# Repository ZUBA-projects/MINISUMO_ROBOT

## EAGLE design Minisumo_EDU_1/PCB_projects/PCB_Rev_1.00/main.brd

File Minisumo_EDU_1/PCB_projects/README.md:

# MINISUMO_ROBOT_EDU1

Mainboard rev 1.10
	
```
	//in future
```

Mainboard rev 1.00

```
Bugs: 
	-bad JST balancer connector size
	-bad color sensor connector pinout
```

Eagle libraries file: https://github.com/ZUBA-projects/ZUBA_EAGLE_LBR

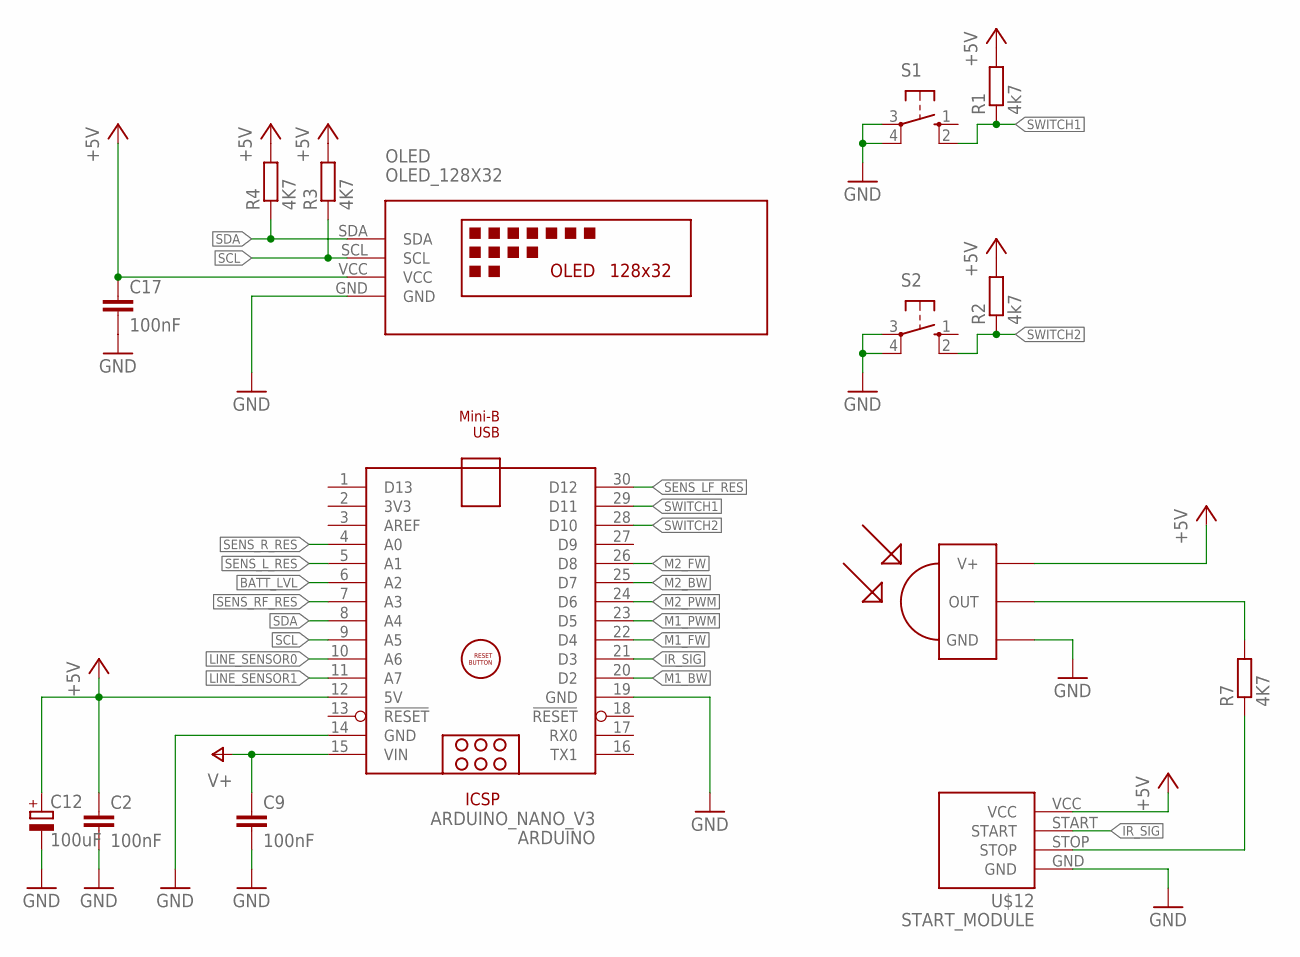
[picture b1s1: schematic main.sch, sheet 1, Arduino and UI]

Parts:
ARDUINO: ARDUINO_NANO_V3
C2, C9, C17: 100nF; C0805
C12: 100uF; E3,5-8
OLED: OLED_128X32; OLED
R1, R2: 4k7; M0805
R3, R4, R7: 4K7; M0805
S1, S2: 10-XX; B3F-10XX
U$2: TSOP4838; TSOP
U$12: START_MODULE

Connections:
+5V: ARDUINO.12 (5V), C2.1, C12.+, C17.1, OLED.VCC, R1.2, R2.2, R3.2, R4.2, U$2.VCC (V+), U$12.VCC; also elsewhere on the board
BATT_LVL: ARDUINO.6 (A2); also elsewhere on the board
GND: ARDUINO.14 (GND), ARDUINO.19 (GND), C2.2, C9.2, C12.-, C17.2, OLED.GND, S1.3, S1.4 (P1), S2.3, S2.4 (P1), U$2.GND, U$12.GND; also elsewhere on the board
IR_SIG: ARDUINO.21 (D3), U$12.START
LINE_SENSOR0: ARDUINO.10 (A6); also elsewhere on the board
LINE_SENSOR1: ARDUINO.11 (A7); also elsewhere on the board
M1_BW: ARDUINO.20 (D2); also elsewhere on the board
M1_FW: ARDUINO.22 (D4); also elsewhere on the board
M1_PWM: ARDUINO.23 (D5); also elsewhere on the board
M2_BW: ARDUINO.25 (D7); also elsewhere on the board
M2_FW: ARDUINO.26 (D8); also elsewhere on the board
M2_PWM: ARDUINO.24 (D6); also elsewhere on the board
unnamed: R7.1, U$12.STOP
unnamed: R7.2, U$2.OUT
SCL: ARDUINO.9 (A5), OLED.SCL, R3.1; also elsewhere on the board
SDA: ARDUINO.8 (A4), OLED.SDA, R4.1; also elsewhere on the board
SENS_LF_RES: ARDUINO.30 (D12); also elsewhere on the board
SENS_L_RES: ARDUINO.5 (A1); also elsewhere on the board
SENS_RF_RES: ARDUINO.7 (A3); also elsewhere on the board
SENS_R_RES: ARDUINO.4 (A0); also elsewhere on the board
SWITCH1: ARDUINO.29 (D11), R1.1, S1.2 (S1)
SWITCH2: ARDUINO.28 (D10), R2.1, S2.2 (S1)
V+: ARDUINO.15 (VIN), C9.1; also elsewhere on the board

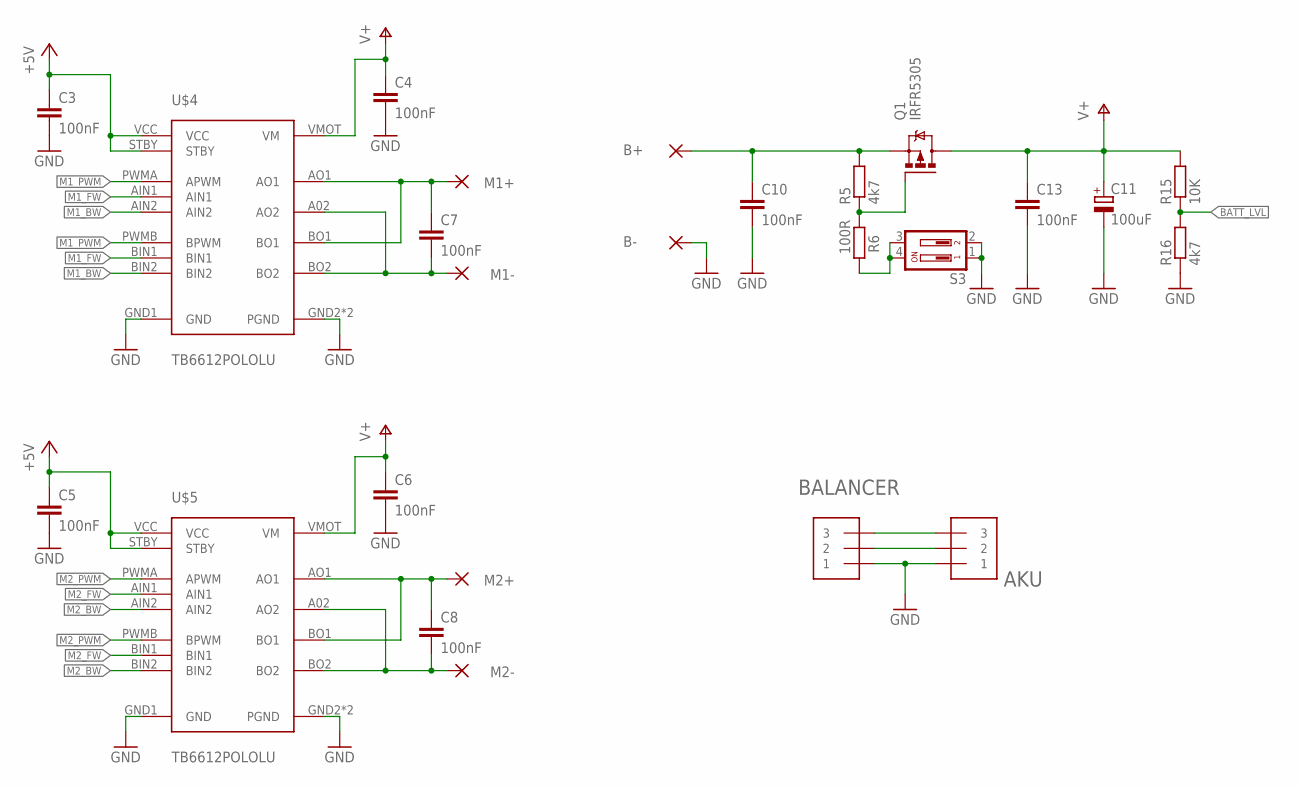
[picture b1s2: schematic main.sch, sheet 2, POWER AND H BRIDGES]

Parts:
AKU: JST_ZH_3
B+: 2,54/1,0
B-: 2,54/1,0
BALANCER: JST_ZH_3
C3, C4, C5, C6, C7, C8, C10, C13: 100nF; C0805
C11: 100uF; E3,5-8
M1+, M1-, M2+, M2-: 2,54/1,0
Q1: IRFR5305; D-PAK_TO252AA
R5, R16: 4k7; M0805
R6: 100R; M0805
R15: 10K; M0805
S3: DS02; DS-02
U$4, U$5: TB6612POLOLU; POLOLU

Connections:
+5V: C3.1, C5.1, U$4.STBY, U$4.VCC, U$5.STBY, U$5.VCC; also elsewhere on the board
BATT_LVL: R15.1, R16.2; also elsewhere on the board
GND: AKU.P$1 (1), B-.1, BALANCER.P$1 (1), C3.2, C4.2, C5.2, C6.2, C10.2, C11.-, C13.2, R16.1, S3.1, S3.2, U$4.GND1 (GND), U$4.GND2 (PGND), U$4.GND3 (PGND), U$5.GND1 (GND), U$5.GND2 (PGND), U$5.GND3 (PGND); also elsewhere on the board
M1_BW: U$4.AIN2, U$4.BIN2; also elsewhere on the board
M1_FW: U$4.AIN1, U$4.BIN1; also elsewhere on the board
M1_PWM: U$4.PWMA (APWM), U$4.PWMB (BPWM); also elsewhere on the board
M2_BW: U$5.AIN2, U$5.BIN2; also elsewhere on the board
M2_FW: U$5.AIN1, U$5.BIN1; also elsewhere on the board
M2_PWM: U$5.PWMA (APWM), U$5.PWMB (BPWM); also elsewhere on the board
unnamed: C7.1, M1+.1, U$4.AO1, U$4.BO1
unnamed: C7.2, M1-.1, U$4.A02 (AO2), U$4.BO2
unnamed: C8.1, M2+.1, U$5.AO1, U$5.BO1
unnamed: C8.2, M2-.1, U$5.A02 (AO2), U$5.BO2
unnamed: Q1.1 (G), R5.1, R6.1
unnamed: R6.2, S3.3, S3.4
unnamed: AKU.P$2 (2), BALANCER.P$2 (2)
unnamed: B+.1, C10.1, Q1.3 (S), R5.2
unnamed: AKU.P$3 (3), BALANCER.P$3 (3)
V+: C4.1, C6.1, C11.+, C13.1, Q1.4 (D), R15.2, U$4.VMOT (VM), U$5.VMOT (VM); also elsewhere on the board

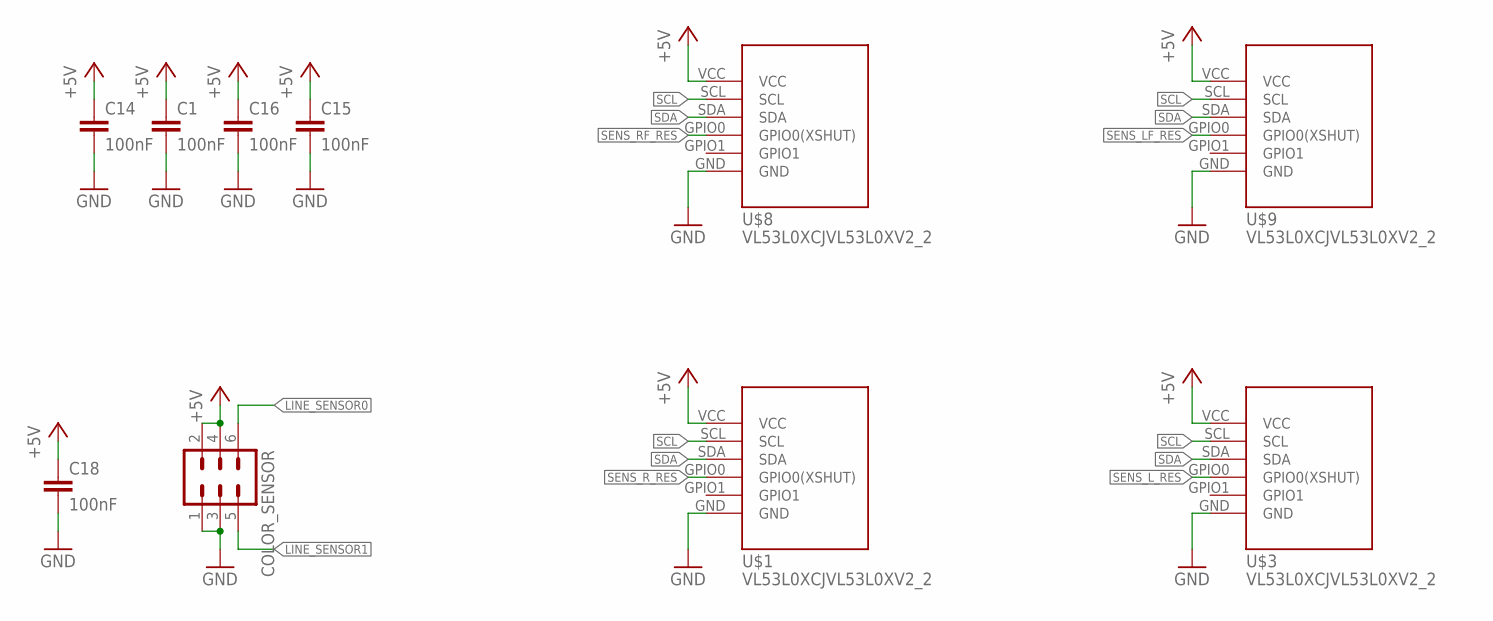
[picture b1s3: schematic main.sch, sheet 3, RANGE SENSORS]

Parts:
C1, C14, C15, C16, C18: 100nF; C0805
COLOR_SENSOR: MA03-2
U$1, U$3, U$8, U$9: VL53L0XCJVL53L0XV2_2; VL53L0X_4

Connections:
+5V: C1.1, C14.1, C15.1, C16.1, C18.1, COLOR_SENSOR.2, COLOR_SENSOR.4, U$1.VCC, U$3.VCC, U$8.VCC, U$9.VCC; also elsewhere on the board
GND: C1.2, C14.2, C15.2, C16.2, C18.2, COLOR_SENSOR.1, COLOR_SENSOR.3, U$1.GND, U$3.GND, U$8.GND, U$9.GND; also elsewhere on the board
LINE_SENSOR0: COLOR_SENSOR.6; also elsewhere on the board
LINE_SENSOR1: COLOR_SENSOR.5; also elsewhere on the board
SCL: U$1.SCL, U$3.SCL, U$8.SCL, U$9.SCL; also elsewhere on the board
SDA: U$1.SDA, U$3.SDA, U$8.SDA, U$9.SDA; also elsewhere on the board
SENS_LF_RES: U$9.GPIO0 (GPIO0(XSHUT)); also elsewhere on the board
SENS_L_RES: U$3.GPIO0 (GPIO0(XSHUT)); also elsewhere on the board
SENS_RF_RES: U$8.GPIO0 (GPIO0(XSHUT)); also elsewhere on the board
SENS_R_RES: U$1.GPIO0 (GPIO0(XSHUT)); also elsewhere on the board

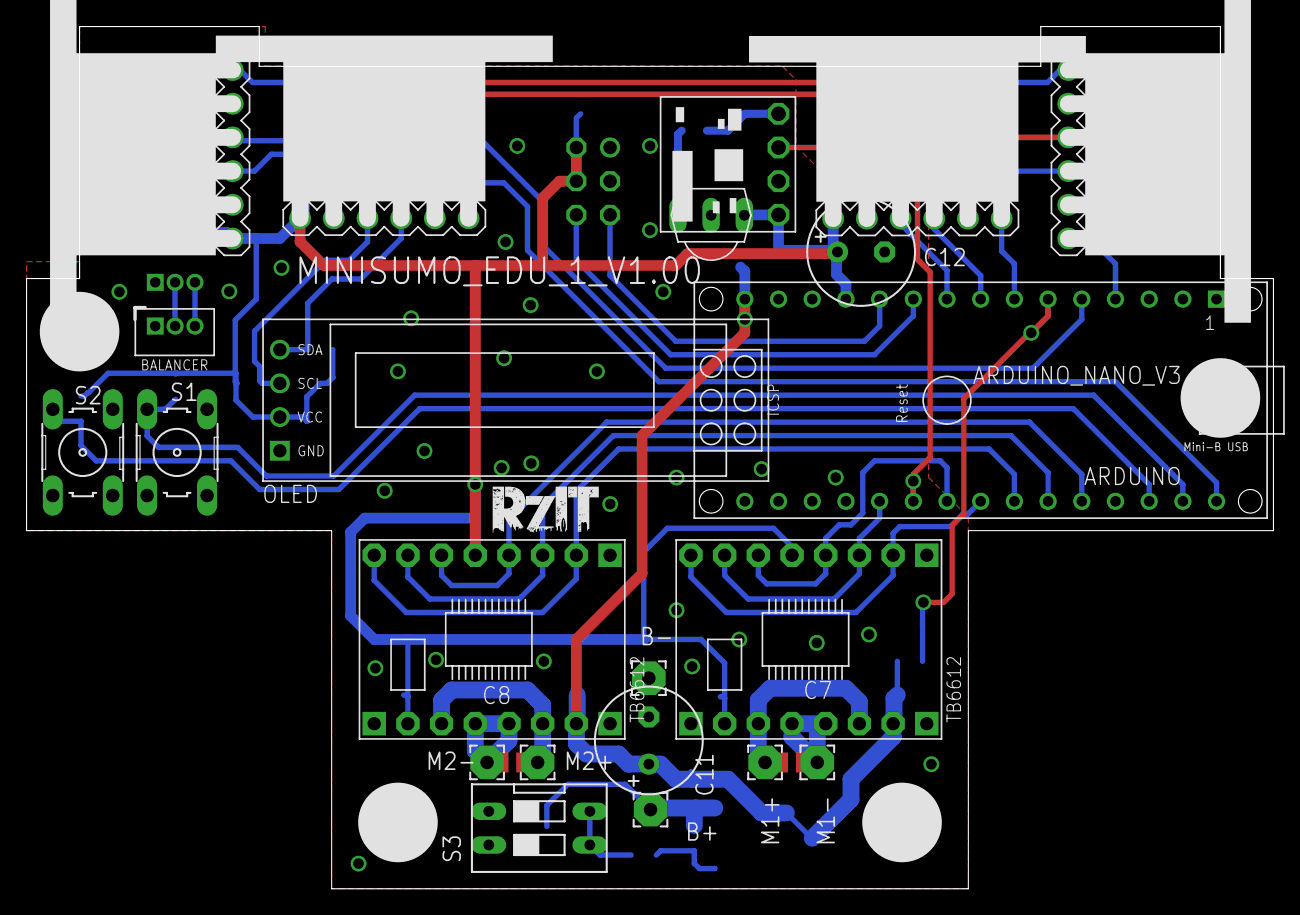
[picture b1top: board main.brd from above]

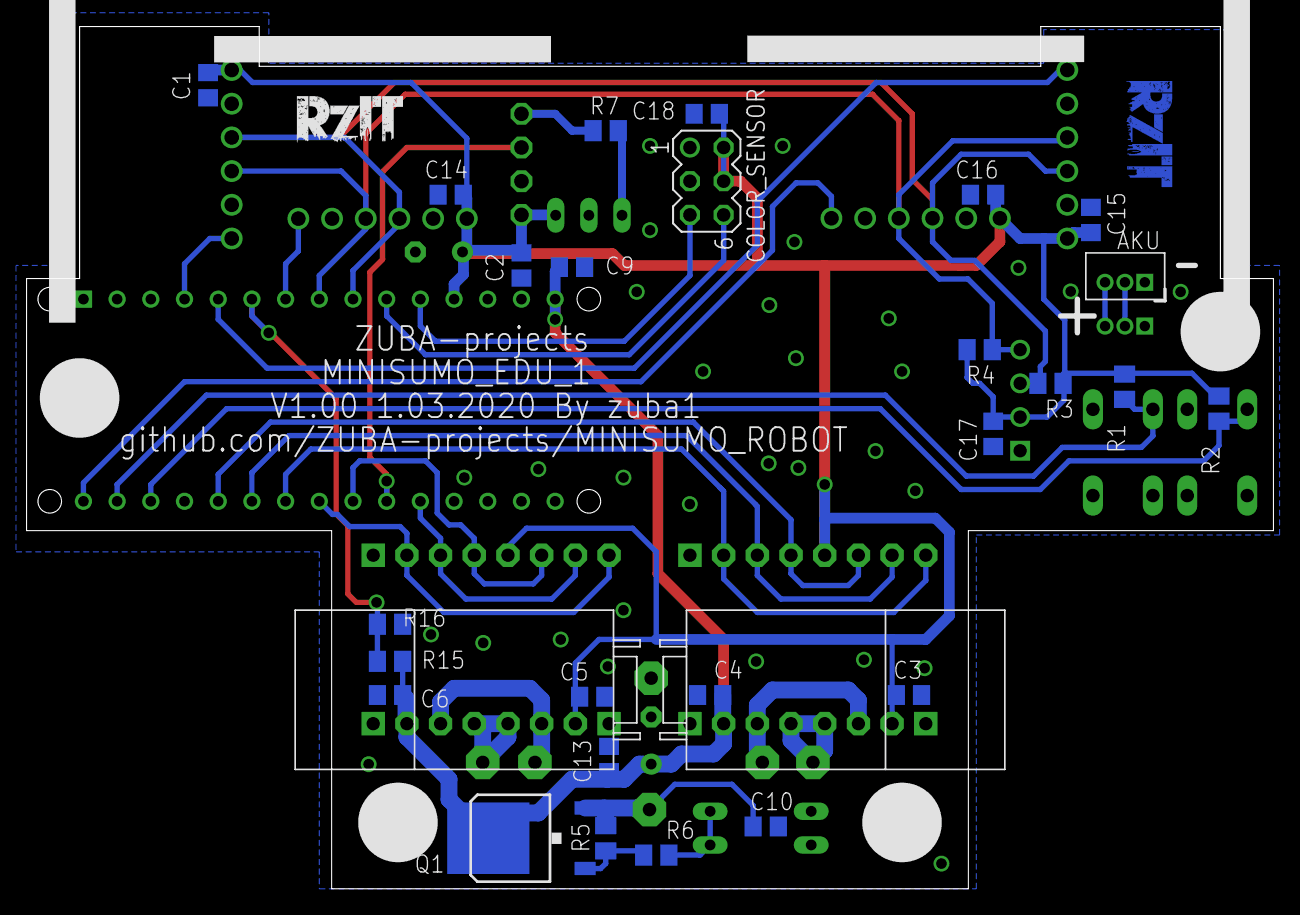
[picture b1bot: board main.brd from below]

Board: 2 copper layers, 94.0 x 65.0 mm, 52 parts (28 on the bottom side), 32 nets.

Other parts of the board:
U$6, U$7: POLOLU_HP

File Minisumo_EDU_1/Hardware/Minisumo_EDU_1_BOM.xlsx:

| Main board:
 | Qty | Value | Parts | Package | LINKS | Price for one | Price
 | 1 | 100R | R6 | M0805 | https://www.tme.eu/pl/details/smd0805-100r/rezystory-smd-080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 | 0.05 | 0.05
 | 1 | 1K | R16 | M0805 | https://www.tme.eu/pl/details/smd0805-1k/rezystory-smd-0805/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 | 0.05 | 0.05
 | 2 | 4K7 | R3, R4 | M0805 | https://www.tme.eu/pl/details/smd0805-4k7/rezystory-smd-0805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 | 0.05 | 0.1
 | 4 | 10K | R1, R2, R5, R15 | M0805 | https://www.tme.eu/pl/details/crcw080510k0fktabc/rezystory-s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 | 0.05 | 0.2
 | 16 | 100nF | C1, C2, C3, C4, C5, C6, C7, C8, C9, C10, C13, C14, C15, C16, C17, C18 | C0805 | https://www.tme.eu/pl/details/cl21b104kbcnnnc/kondensatory-m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 | 8.4000000000000005E-2 | 1.3440000000000001
 | 2 | 47uF | C11, C12 | E3,5-8 | https://www.tme.eu/pl/details/ce-47_50pht/kondensatory-elekt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 | 0.307 | 0.61399999999999999
 | 1 | IRFR5305 or similar | Q1 | D-PAK_TO252AA | https://www.tme.eu/pl/details/std46p4llf6/tranzystory-z-kana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 | 3.8 | 3.8
 | 1 | TSOP4838 | U$2 | TSOP | https://www.tme.eu/pl/details/tsop4838/moduly-odbiorcze-ir/vishay/ | 2.21 | 2.21
 | 1 | START_MODULE | U$12 | START_MODULE | https://p1r.se/startmodule/ |  |  | use this module if TSOP4838 is not used
 | 1 | power switch | S3 | DS-02 | https://www.tme.eu/pl/details/ds-02/przelaczniki-typu-dip-sw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 | 2.16 | 2.16
 | 2 | function switch | S1, S2 | B3F-10XX | https://www.tme.eu/pl/details/evqpac09k/mikroprzelaczniki-ta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 | 0.63 | 1.26
 | 2 | JST_ZH_3 | AKU, BALANCER | JST_ZH_3 | https://www.tme.eu/pl/details/b3b-ph-k-s/zlacza-sygnalowe-ra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 | 0.6 | 1.2
 | 4 | VL53L0XCJ_2 | U$1, U$3, U$8, U$9 | Only Connector | https://www.tme.eu/pl/details/zl263-6sg/listwy-i-gniazda-kol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 | 0.6 | 2.4
 | 4 | VL53L0XCJ_2 | U$1, U$3, U$8, U$9 | VL53L0X_4 | http://pl.aliexpress.com/item/4000163323280.html?spm=a2g0o.p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 | 13 | 52
 | 4 | TB6612POLOLU | U$4, U$5 | Only Connector | https://www.tme.eu/pl/details/zl262-8sg/listwy-i-gniazda-kol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 | 0.35 | 1.4
 | 2 | TB6612POLOLU | U$4, U$5 | POLOLU | https://www.tme.eu/pl/details/pololu-713/modulowe-sterowniki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 | 16.43 | 32.86
 | 1 | Color sensor conn | COLOR_SENSOR | MA03-2 | https://www.tme.eu/pl/details/pololu-2458/czujniki-odleglosc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 | 15.61 | 15.61
 | 2 | ARDUINO_NANO_V3 | ARDUINO | Only Connector | https://www.tme.eu/pl/details/zl262-16sg/listwy-i-gniazda-ko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 | 0.72 | 1.44
 | 1 | ARDUINO_NANO_V3 | ARDUINO | ARDUINO_NANO_V3 | http://pl.aliexpress.com/item/32323945639.html?spm=a2g0o.pro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 | 10 | 10
 | 1 | OLED_128X32 | OLED | OLED | http://pl.aliexpress.com/item/32661842518.html?spm=a2g0o.pro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 | 6.42 | 6.42
 | 1 | aku connector | B+ B- | LiPol | https://abc-rc.pl/product-pol-692-Wtyk-JST-BEC-z-przewodem-z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 | 1 | 1
 |  |  |  |  | price: |  | 136.11799999999999
 | and create charging cable:
 |  |  |  |  | https://www.tme.eu/pl/details/phr-3/zlacza-sygnalowe-raster-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
 |  |  |  |  | https://www.tme.eu/pl/details/sph-002t-p0.5s/zlacza-sygnalow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

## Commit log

2020-02-19 BETA Version of Minisumo robot EDU_1. Bad arduino 3d model, need some changes in pcb and some bugs in 3d model
2020-02-19 md file error
2020-02-19 no message
2020-02-20 google testing...
2020-03-08 V1.0 No software
2020-03-08 added correct image paths
2020-03-10 Added new bom. Fixed mechanical problem.
2020-04-05 Test of circuit. Oled, ADC and TOF sensor powered by Arduino Libs
2020-04-05 edit
2020-04-18 Added new oled and vl53l0x sensor lib's. Some Arduino core code. Temporary two code versions in testing (Arduino and my_HAL version).
2020-06-08 Final 3d model V1, final pcb model V1.00, Software version 0.32 (uncomplete -only for testing). New files organization
2020-06-08 fix md files
2020-06-08 another md fix
2020-06-08 again trying to fix md files

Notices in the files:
parts and their libraries:
SparkFun-Aesthetics: Licensing: Creative Commons ShareAlike 4.0 International - https://creativecommons.org/licenses/by-sa/4.0
